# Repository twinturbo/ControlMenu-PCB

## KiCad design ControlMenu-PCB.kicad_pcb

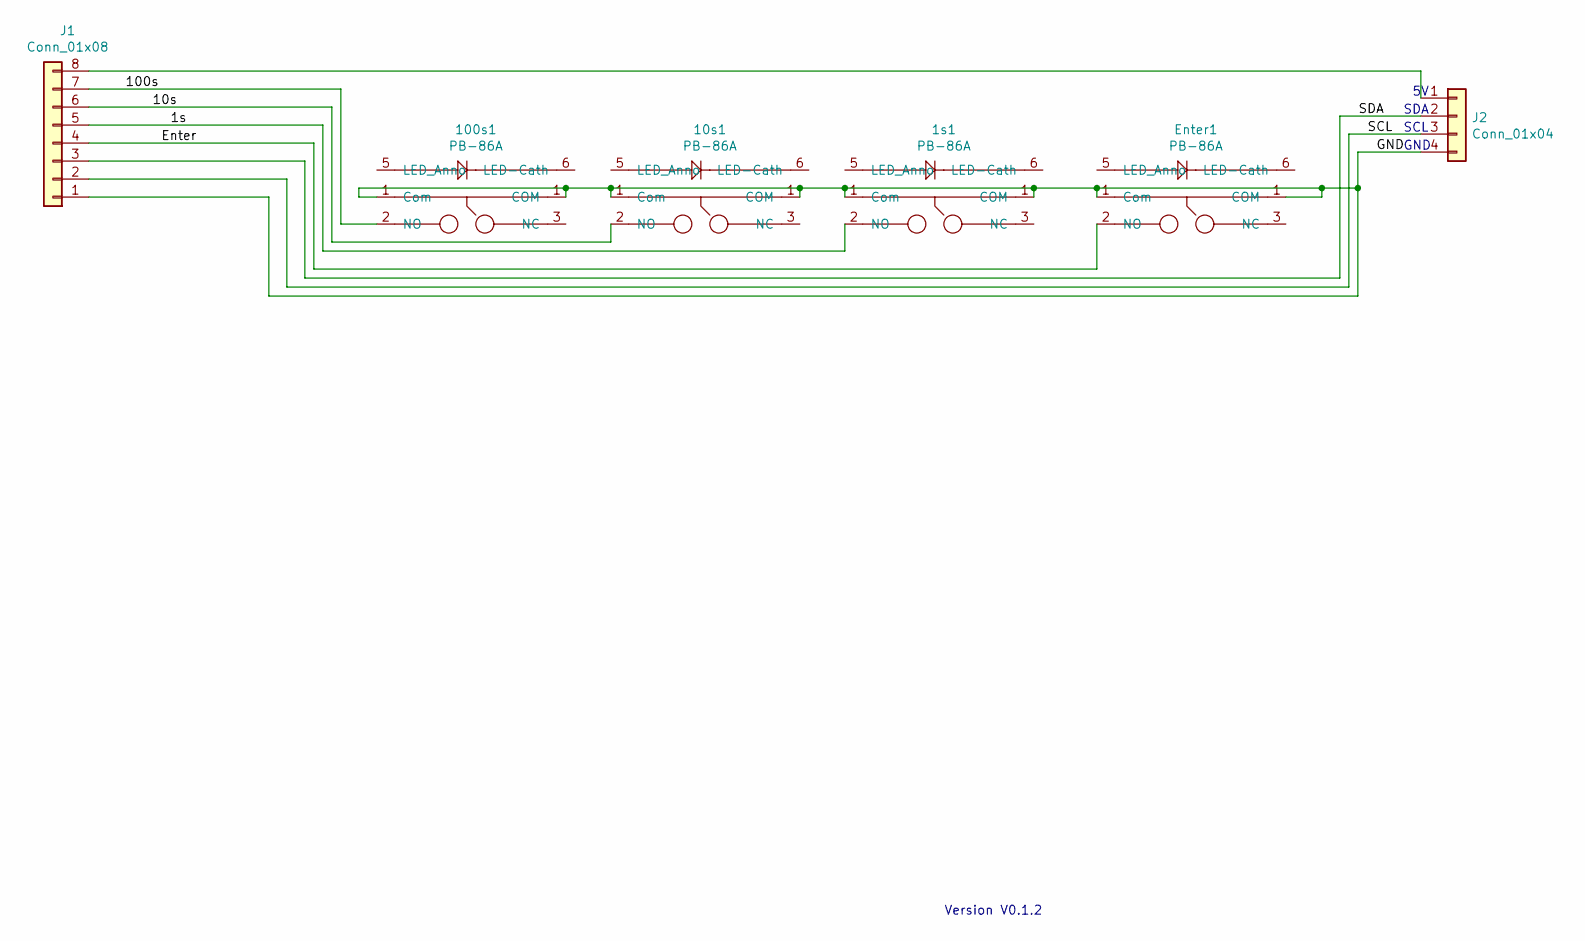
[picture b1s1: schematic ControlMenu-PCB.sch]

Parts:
1s1, 10s1, 100s1: PB-86A; PB86-A-FP
Enter1: PB-86A; PB86-A-FP
J1: Conn_01x08; PinHeader_1x08_P2.54mm_Vertical
J2: Conn_01x04; PinHeader_1x04_P2.54mm_Horizontal

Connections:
/1s: 1s1.2 (NO), J1.5
/10s: 10s1.2 (NO), J1.6
/100s: 100s1.2 (NO), J1.7
/Enter: Enter1.2 (NO), J1.4
/GND: 1s1.1 (Com), 10s1.1 (Com), 100s1.1 (Com), Enter1.1 (Com), J1.1, J2.4
/SCL: J1.2, J2.3
/SDA: J1.3, J2.2
unnamed: J1.8, J2.1

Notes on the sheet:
SDA
SCL
GND
Version V0.1.2

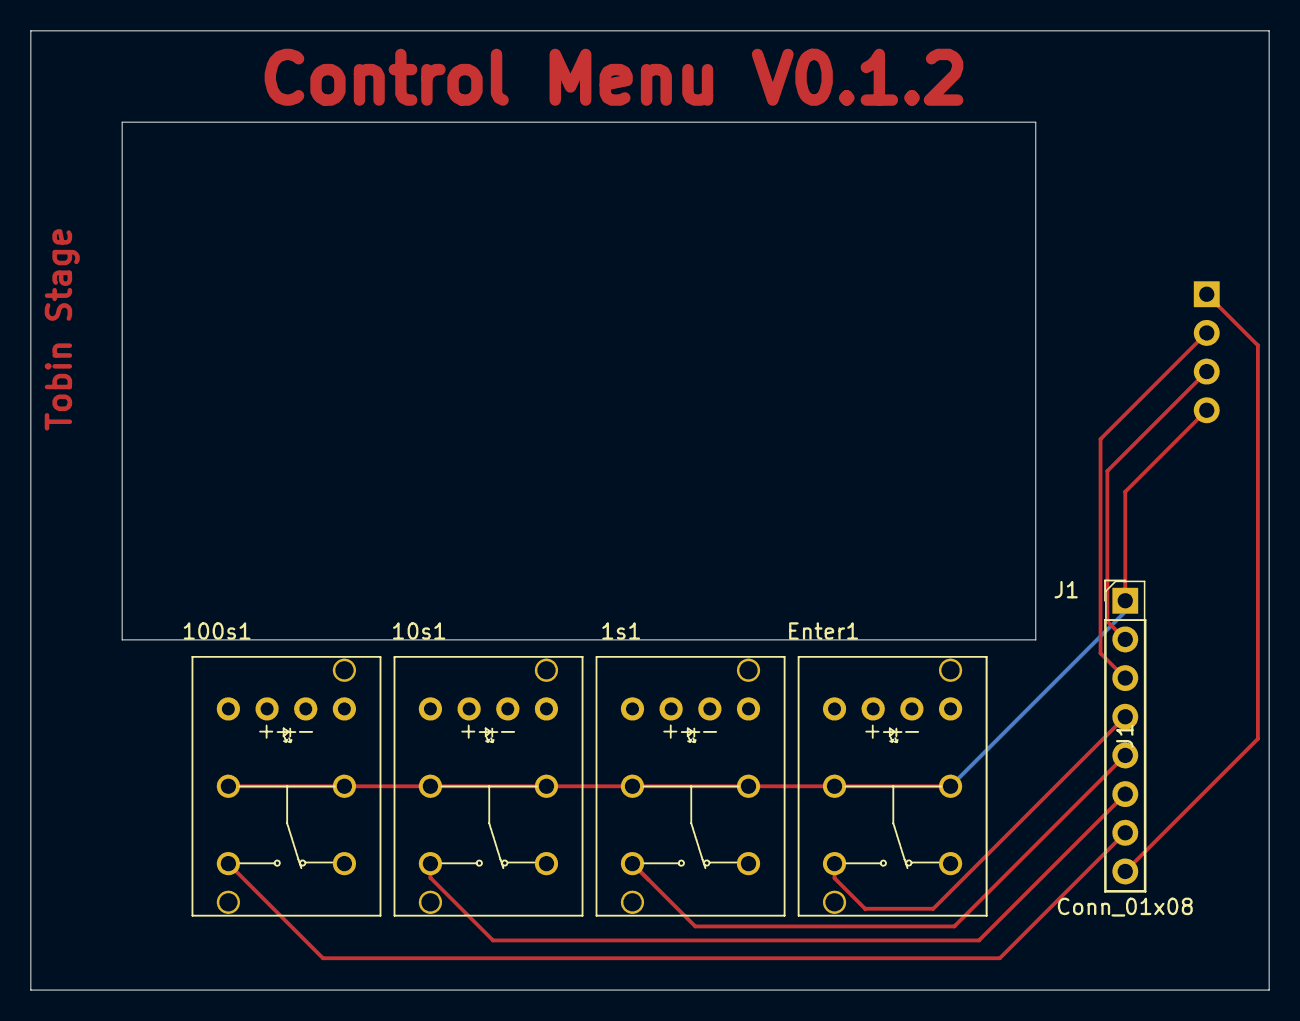
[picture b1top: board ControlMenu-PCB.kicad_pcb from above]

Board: 2 copper layers, 81.3 x 63.0 mm, 6 parts (1 on the bottom side), 8 nets.

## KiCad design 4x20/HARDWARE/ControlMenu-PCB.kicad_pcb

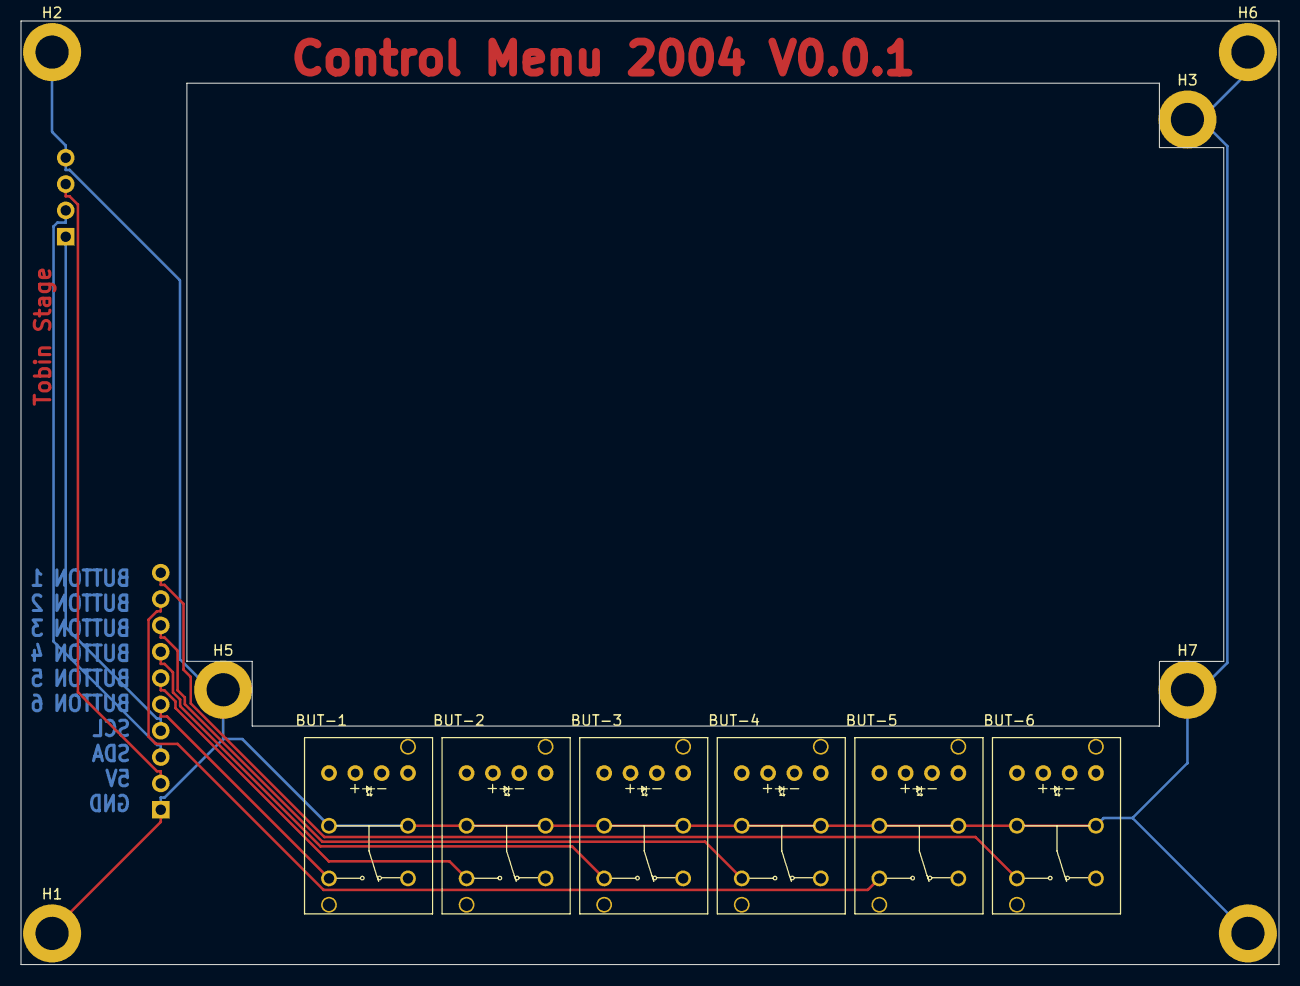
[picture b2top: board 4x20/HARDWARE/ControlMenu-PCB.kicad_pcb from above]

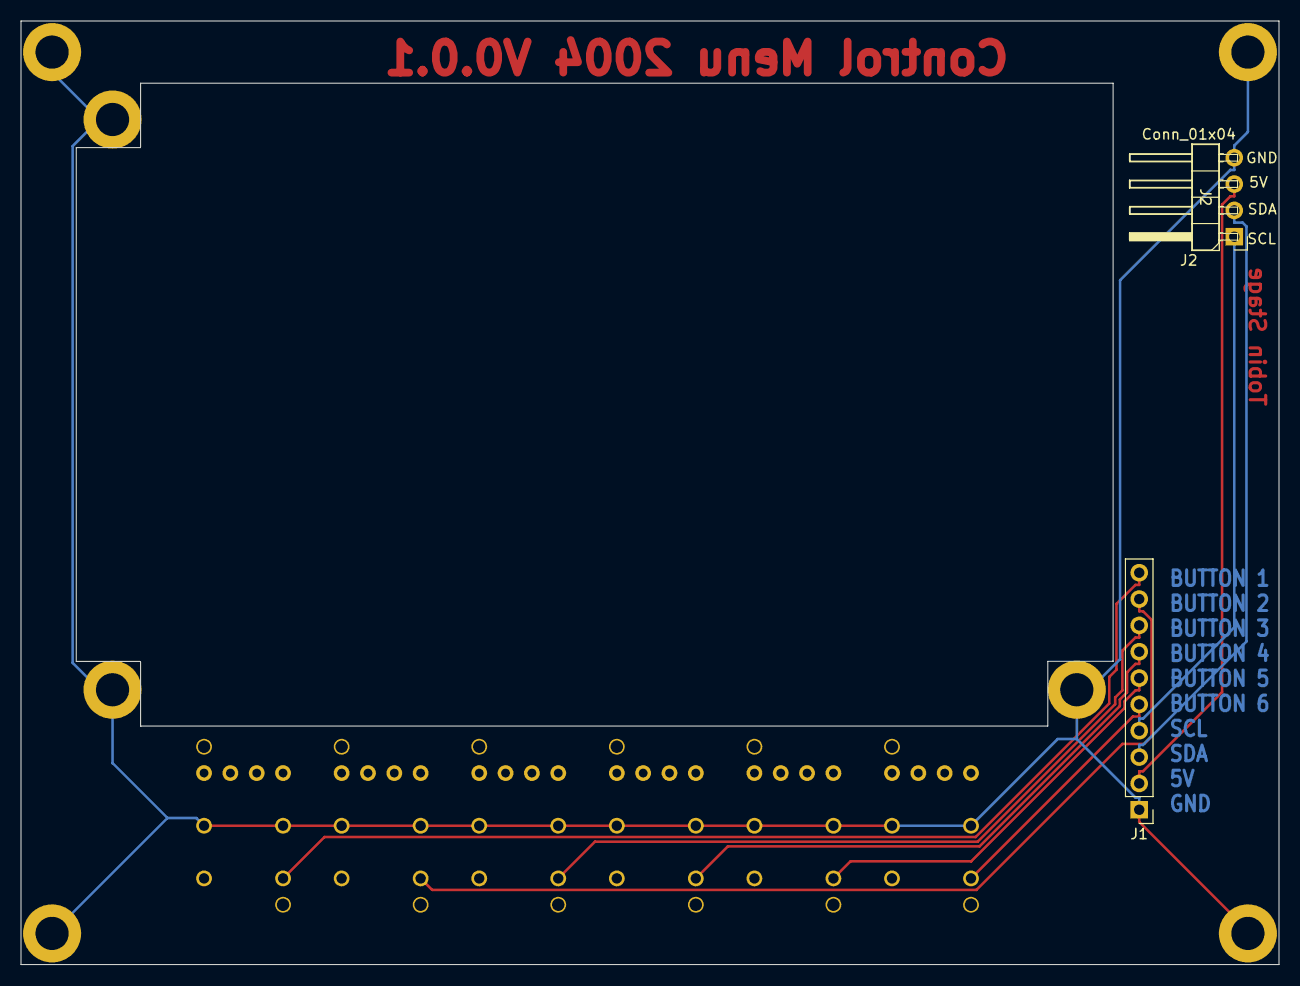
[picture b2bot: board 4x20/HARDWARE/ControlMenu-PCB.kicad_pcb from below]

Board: 2 copper layers, 121.3 x 91.0 mm, 15 parts (2 on the bottom side), 10 nets.

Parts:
BUT-1, BUT-2, BUT-3, BUT-4, BUT-5, BUT-6: PB-86A; PB86-A-FP
H1, H2, H3, H4, H5, H6, H7: MountingHole_Pad; MountingHole_3.2mm_M3_DIN965_Pad
J1: Conn_01x10; PinHeader_1x10_P2.54mm_Vertical
J2: Conn_01x04; PinHeader_1x04_P2.54mm_Horizontal

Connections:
+5V: J1.2, J2.3
BUTTON1: BUT-1.2 (NO), J1.5
BUTTON2: BUT-2.2 (NO), J1.6
BUTTON3: BUT-3.2 (NO), J1.7
BUTTON4: BUT-4.2 (NO), J1.8
BUTTON5: BUT-5.2 (NO), J1.9
BUTTON6: BUT-6.2 (NO), J1.10
GND: BUT-1.1 (COM), BUT-2.1 (COM), BUT-3.1 (COM), BUT-4.1 (COM), BUT-5.1 (COM), BUT-6.1 (COM), H1.1, H2.1, H3.1, H4.1, H5.1, H6.1, H7.1, J1.1, J2.4
SCL: J1.4, J2.1
SDA: J1.3, J2.2

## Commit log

2020-12-26 Initialised
2020-12-26 Clean
2020-12-29 V0.1.0
2020-12-29 LayerFix
2020-12-29 Front
2020-12-29 PCB Routed Manualy
2020-12-29 Schematic Fix
2020-12-29 autosync
2021-01-21 5V to Ground Fixes
2021-02-09 FP fix
2022-01-29 Screen mount cutout reduced, I2C re-ordered.
2022-02-07 Combined
2022-02-19 Ready To Send To Print
2022-02-21 Printed
2025-11-12 MAINSYNC
